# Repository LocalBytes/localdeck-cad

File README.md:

# LocalDeck CAD

## About

See exactly how the LocalDeck is put together, design your own accessories, or suggest improvements to the next revision.
These are the same mechanical and electrical design files we use to build it.

| Folder | Tool | Contents |
|---|---|---|
| [freecad](./freecad) | FreeCAD 1.1 | Enclosure, stand, key caps, moulds, and jigs. Start with [asm-localdeck](./freecad/asm-localdeck.FCStd) |
| [kicad](./kicad) | KiCad 10 | Schematic (including the face plate sheet) and PCB. The ESP32 mini footprint library is a Git submodule |

Looking to set up your LocalDeck rather than look inside it? Head to [LocalBytes Blog / KB / Refs: LocalDeck](https://blog.mylocalbytes.com/kb/2024-04-01/refs-localdeck).

## Getting started

The FreeCAD files in this repo are stored through a Git filter, so set up [Zippey](#zippey) **before** you clone.
Then clone with submodules:

```sh
git clone --recurse-submodules git@github.com:LocalBytes/localdeck-cad.git
```

Please clone the repo rather than downloading files from GitHub.
A download gives you Zippey's text format, not a file FreeCAD can open.

### Zippey

`.FCStd` files are zip archives, which Git can't diff or store efficiently.
This repo runs them through [Zippey](https://github.com/rockstorm101/zippey), which stores them unzipped and rebuilds the archive on checkout.
That way, each save only adds what actually changed.

You'll need Python on your `PATH`. Set it up once per machine:

```sh
curl -fsSL https://raw.githubusercontent.com/rockstorm101/zippey/master/zippey.py -o ~/.local/bin/zippey.py --create-dirs
git config --global filter.zippey.clean  "python ~/.local/bin/zippey.py e"
git config --global filter.zippey.smudge "python ~/.local/bin/zippey.py d"
git config --global filter.zippey.required true
```

The `required` setting makes Git stop with an error if the filter is missing, rather than quietly committing raw archives.

If you cloned before setting this up, rebuild the files with:

```sh
git ls-files -z '*.FCStd' | xargs -0 rm -f && git checkout -- '*.FCStd'
```

### Readable diffs (optional)

FreeCAD's fcinfo tool turns an `.FCStd` into a summary of each object, so `git diff` shows what changed rather than raw XML.
Install it globally, and it works in any repo:

```sh
curl -fsSL https://raw.githubusercontent.com/FreeCAD/FreeCAD/main/src/Tools/fcinfo -o ~/.local/bin/fcinfo --create-dirs
git config --global diff.fcinfo.textconv "python ~/.local/bin/fcinfo"
echo '*.FCStd diff=fcinfo' >> ~/.config/git/attributes
```

FreeCAD updates metadata such as `LastModifiedDate` on every save, so expect a few lines of that in each diff.
[GitHub / FreeCAD | src/Tools/fcinfo](https://github.com/FreeCAD/FreeCAD/blob/main/src/Tools/fcinfo)

## Contributing

Found a problem with the design, or have an idea for an improvement? [Open an issue](https://github.com/LocalBytes/localdeck-cad/issues) and tell us about it.
You'll also find plenty of LocalDeck owners on the [LocalBytes Forum](https://forum.mylocalbytes.com/), and we'd love your input there when we ask for feedback on something new.

Please talk to us in an issue before opening a pull request.
CAD files are hard to review and can't be merged like code, so we'd rather agree on a change first.
Anything you contribute becomes the property of Allport-IT LTD.

## Licence

This project is currently published with no specific licence:
- It is distributed in the hope that it will be useful, but WITHOUT ANY WARRANTY
- As an individual, you are free to learn from it and use it in your own projects
- You must not claim it as your own

Unless otherwise stated, all code is &copy; Allport-IT LTD. All rights reserved.  
"LocalBytes" and the LocalBytes Logo are &reg; of Allport-IT LTD.

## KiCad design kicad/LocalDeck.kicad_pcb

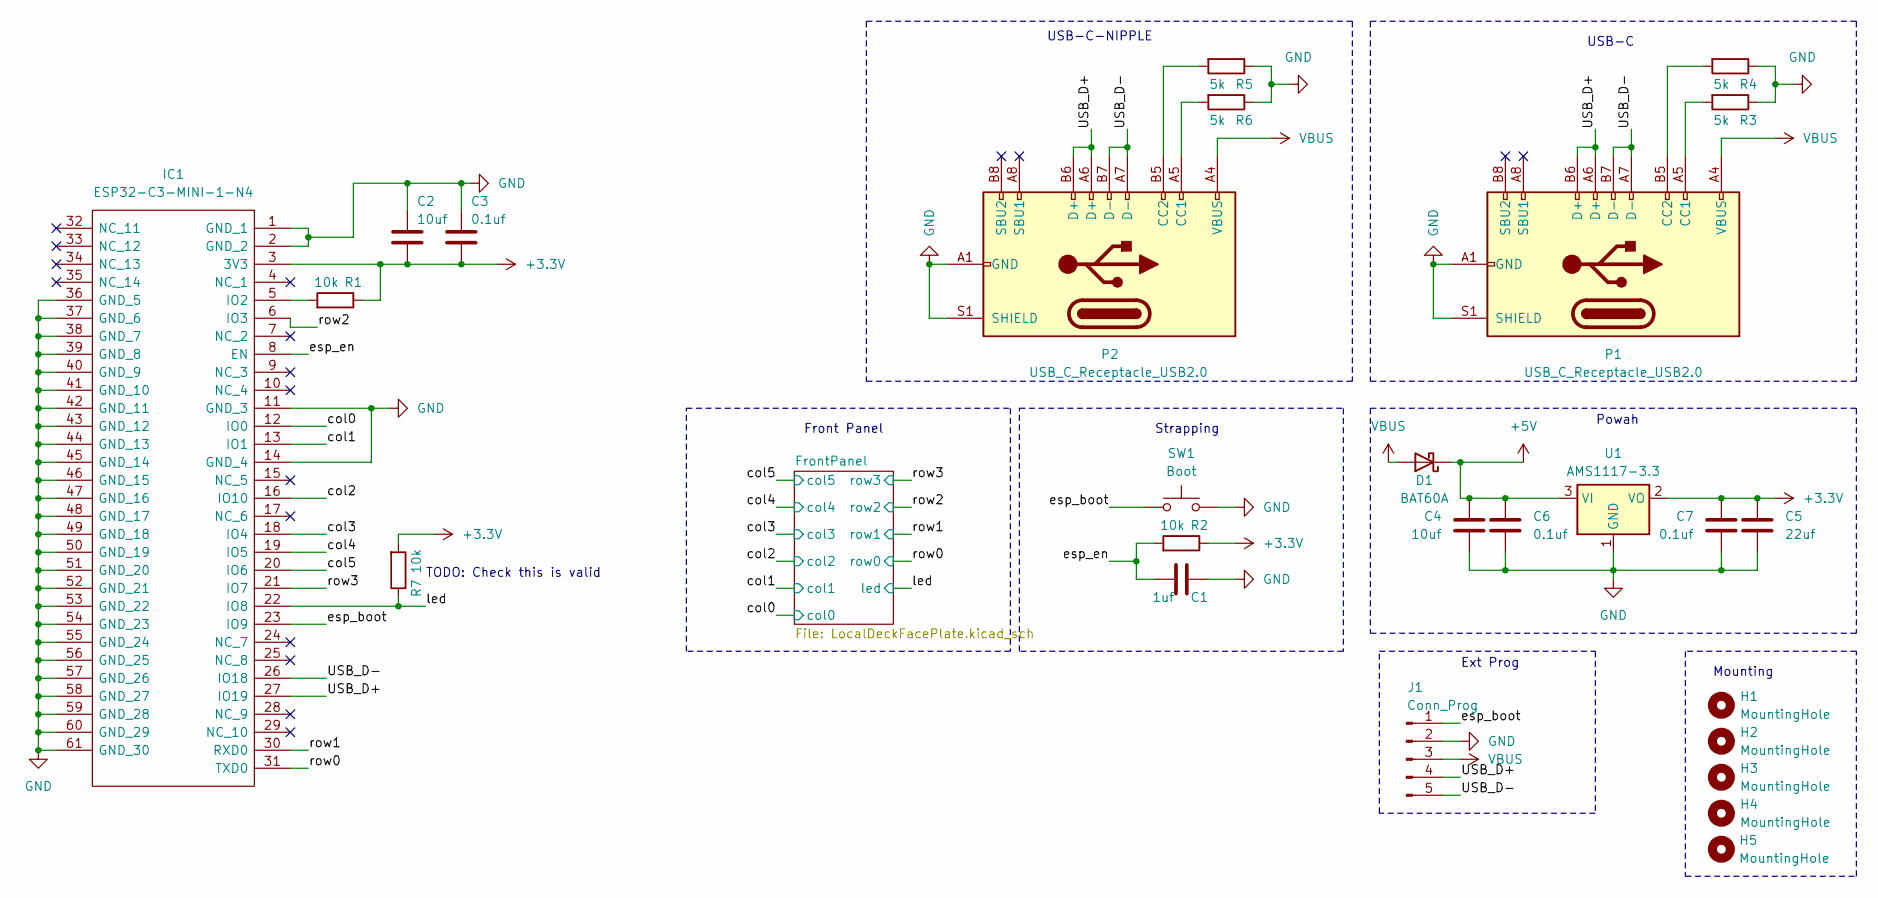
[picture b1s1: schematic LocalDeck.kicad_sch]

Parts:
C1: 1uf; C_0603_1608Metric
C2, C4: 10uf; C_0603_1608Metric
C3, C6, C7: 0.1uf; C_0603_1608Metric
C5: 22uf; C_0603_1608Metric
D1: BAT60A; D_SOD-323; JLCPCB Part C3018529
H1, H2, H3, H4, H5: MountingHole; MountingHole_3.2mm_M3
IC1: ESP32-C3-MINI-1-N4; ESP32C3MINI1N4; Manufacturer_Part_Number ESP32-C3-MINI-1-N4; Mouser Part Number 356-ESP32-C3-MINI1N4
J1: Conn_Prog; ProgrammingHeader
P1: USB_C_Receptacle_USB2.0; USB_C_Receptacle_HRO_TYPE-C-31-M-12; JLCPCB Part C165948
P2: USB_C_Receptacle_USB2.0; USB_C_Receptacle_GCT_USB4115-03-C; JLCPCB Part C2977724
R1, R2, R7: 10k; R_0603_1608Metric
R3, R4, R5, R6: 5k; R_0603_1608Metric
SW1: Boot; SW_Push_1P1T_XKB_TS-1187A; Part # TS-1187A-B-A-B; JLCPCB Part C318884
U1: AMS1117-3.3; SOT-223-3_TabPin2

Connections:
+3.3V: C2.2, C3.2, C5.1, C7.1, IC1.3 (3V3), R1.1, R2.1, R7.2, U1.2 (VO)
+5V: C4.1, C6.1, D1.1 (K), U1.3 (VI); also elsewhere on the board
/USB_D+: IC1.27 (IO19), J1.4, P1.A6 (D+), P1.B6 (D+), P2.A6 (D+), P2.B6 (D+)
/USB_D-: IC1.26 (IO18), J1.5, P1.A7 (D-), P1.B7 (D-), P2.A7 (D-), P2.B7 (D-)
/col0: IC1.12 (IO0); also elsewhere on the board
/col1: IC1.13 (IO1); also elsewhere on the board
/col2: IC1.16 (IO10); also elsewhere on the board
/col3: IC1.18 (IO4); also elsewhere on the board
/col4: IC1.19 (IO5); also elsewhere on the board
/col5: IC1.20 (IO6); also elsewhere on the board
/esp_boot: IC1.23 (IO9), J1.1, SW1.2
/esp_en: C1.1, IC1.8 (EN), R2.2
/led: IC1.22 (IO8), R7.1; also elsewhere on the board
/row0: IC1.31 (TXD0); also elsewhere on the board
/row1: IC1.30 (RXD0); also elsewhere on the board
/row2: IC1.6 (IO3); also elsewhere on the board
/row3: IC1.21 (IO7); also elsewhere on the board
GND: C1.2, C2.1, C3.1, C4.2, C5.2, C6.2, C7.2, IC1.1 (GND_1), IC1.2 (GND_2), IC1.11 (GND_3), IC1.14 (GND_4), IC1.36 (GND_5), IC1.37 (GND_6), IC1.38 (GND_7), IC1.39 (GND_8), IC1.40 (GND_9), IC1.41 (GND_10), IC1.42 (GND_11), IC1.43 (GND_12), IC1.44 (GND_13), IC1.45 (GND_14), IC1.46 (GND_15), IC1.47 (GND_16), IC1.48 (GND_17), IC1.49 (GND_18), IC1.50 (GND_19), IC1.51 (GND_20), IC1.52 (GND_21), IC1.53 (GND_22), IC1.54 (GND_23), IC1.55 (GND_24), IC1.56 (GND_25), IC1.57 (GND_26), IC1.58 (GND_27), IC1.59 (GND_28), IC1.60 (GND_29), IC1.61 (GND_30), J1.2, P1.A1 (GND), P1.A12 (GND), P1.B1 (GND), P1.B12 (GND), P1.S1 (SHIELD), P2.A1 (GND), P2.A12 (GND), P2.B1 (GND), P2.B12 (GND), P2.S1 (SHIELD), R3.1, R4.1, R5.1, R6.1, SW1.1, U1.1 (GND); also elsewhere on the board
unnamed: IC1.5 (IO2), R1.2
unnamed: P1.A5 (CC1), R3.2
unnamed: P1.B5 (CC2), R4.2
unnamed: P2.A5 (CC1), R6.2
unnamed: P2.B5 (CC2), R5.2
VBUS: D1.2 (A), J1.3, P1.A4 (VBUS), P1.A9 (VBUS), P1.B4 (VBUS), P1.B9 (VBUS), P2.A4 (VBUS), P2.A9 (VBUS), P2.B4 (VBUS), P2.B9 (VBUS)

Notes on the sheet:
Powah
Mounting
Ext Prog
USB-C
USB-C-NIPPLE
Front Panel
Strapping
TODO: Check this is valid

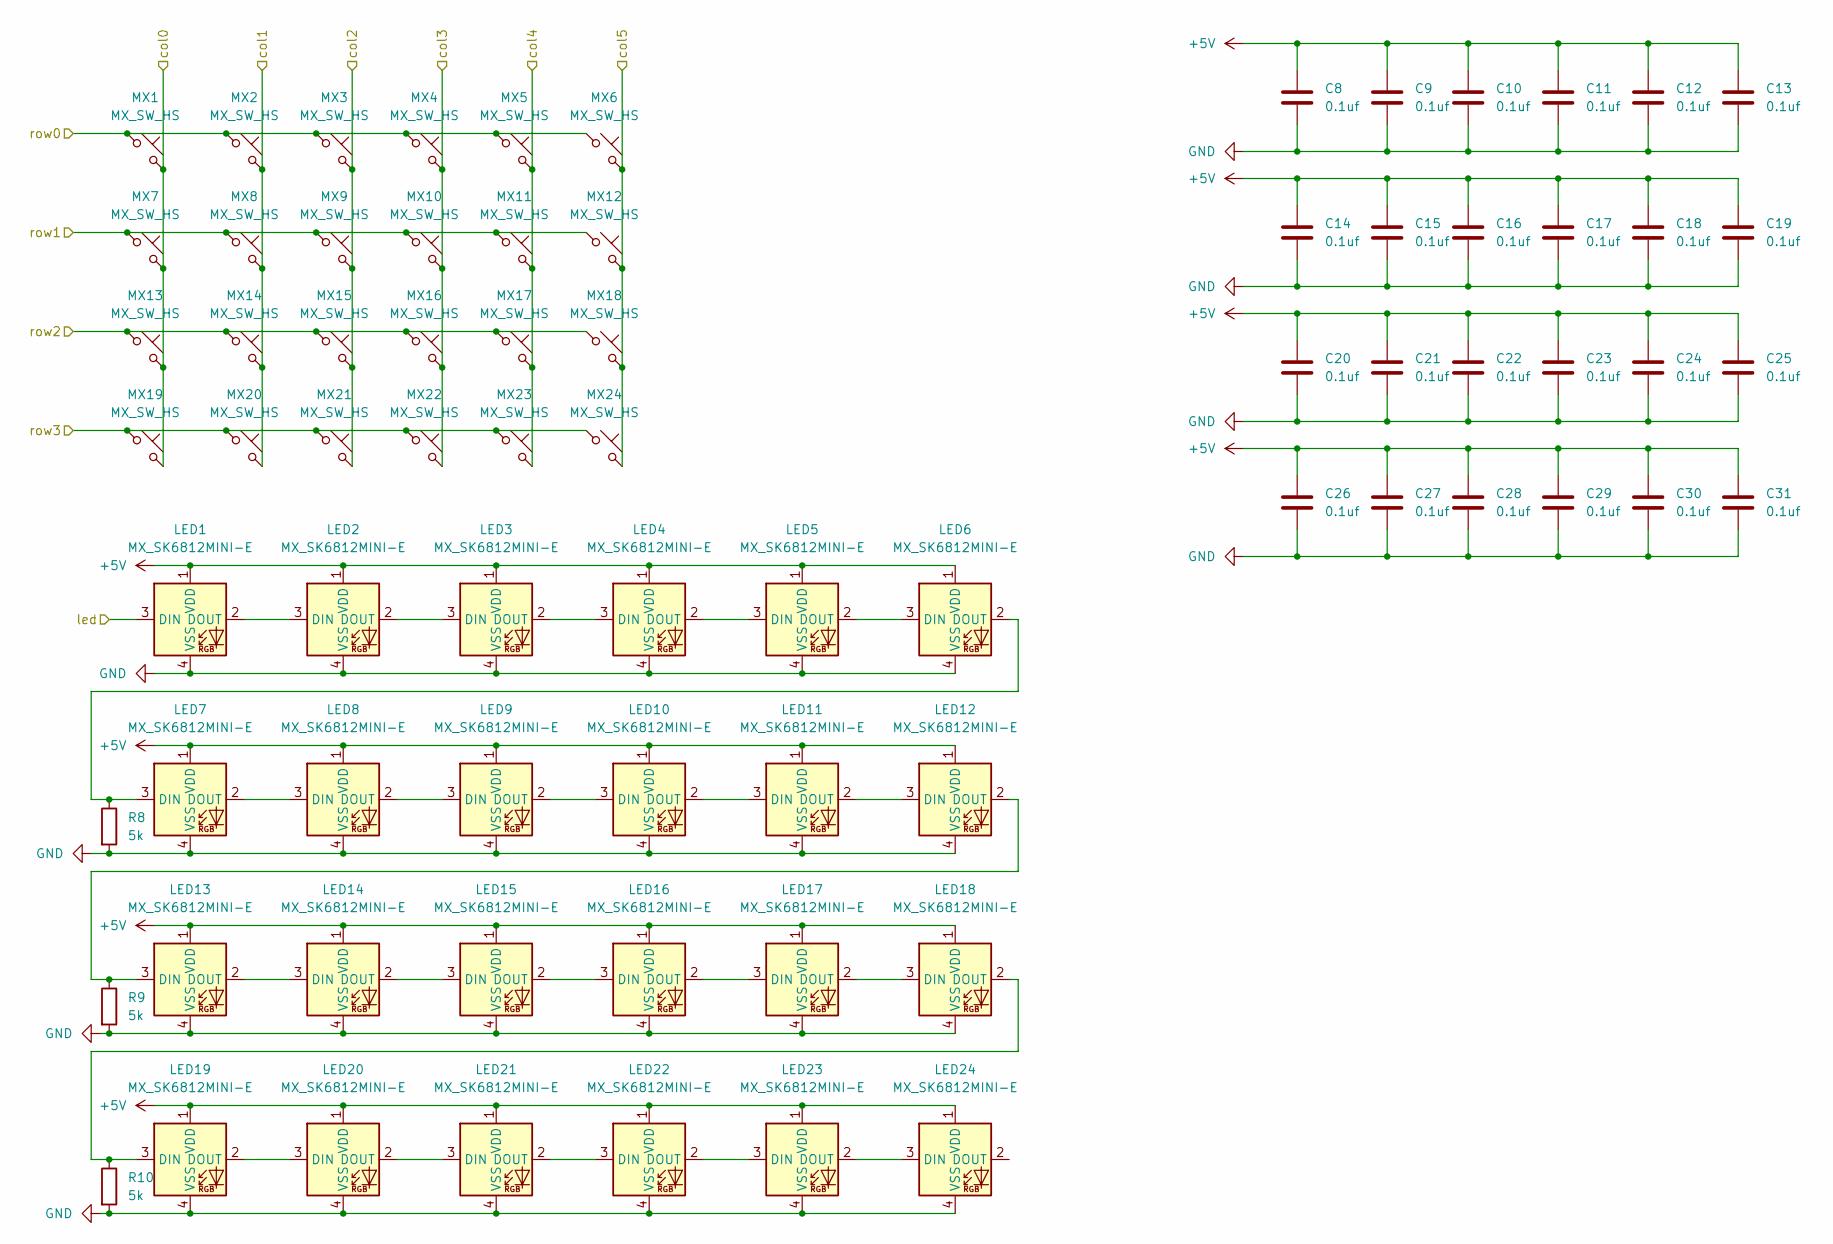
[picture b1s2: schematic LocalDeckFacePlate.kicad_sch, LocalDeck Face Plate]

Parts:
C8, C9, C10, C11, C12, C13, C14, C15, C16, C17, C18, C19, C20, C21, C22, C23, C24, C25, C26, C27, C28, C29, C30, C31: 0.1uf; C_0603_1608Metric
LED1, LED2, LED3, LED4, LED5, LED6, LED7, LED8, LED9, LED10, LED11, LED12, LED13, LED14, LED15, LED16, LED17, LED18, LED19, LED20, LED21, LED22, LED23, LED24: MX_SK6812MINI-E; LED_MX_6028R-ROT; JLCPCB Part C5149201
MX1, MX2, MX3, MX4, MX5, MX6, MX7, MX8, MX9, MX10, MX11, MX12, MX13, MX14, MX15, MX16, MX17, MX18, MX19, MX20, MX21, MX22, MX23, MX24: MX_SW_HS; SW_MX_HS_1u; JLCPCB Part C5156480
R8, R9, R10: 5k; R_0603_1608Metric

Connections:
+5V: C8.1, C9.1, C10.1, C11.1, C12.1, C13.1, C14.1, C15.1, C16.1, C17.1, C18.1, C19.1, C20.1, C21.1, C22.1, C23.1, C24.1, C25.1, C26.1, C27.1, C28.1, C29.1, C30.1, C31.1, LED1.1 (VDD), LED2.1 (VDD), LED3.1 (VDD), LED4.1 (VDD), LED5.1 (VDD), LED6.1 (VDD), LED7.1 (VDD), LED8.1 (VDD), LED9.1 (VDD), LED10.1 (VDD), LED11.1 (VDD), LED12.1 (VDD), LED13.1 (VDD), LED14.1 (VDD), LED15.1 (VDD), LED16.1 (VDD), LED17.1 (VDD), LED18.1 (VDD), LED19.1 (VDD), LED20.1 (VDD), LED21.1 (VDD), LED22.1 (VDD), LED23.1 (VDD), LED24.1 (VDD); also elsewhere on the board
/col0: MX1.2, MX7.2, MX13.2, MX19.2; also elsewhere on the board
/col1: MX2.2, MX8.2, MX14.2, MX20.2; also elsewhere on the board
/col2: MX3.2, MX9.2, MX15.2, MX21.2; also elsewhere on the board
/col3: MX4.2, MX10.2, MX16.2, MX22.2; also elsewhere on the board
/col4: MX5.2, MX11.2, MX17.2, MX23.2; also elsewhere on the board
/col5: MX6.2, MX12.2, MX18.2, MX24.2; also elsewhere on the board
/led: LED1.3 (DIN); also elsewhere on the board
/row0: MX1.1, MX2.1, MX3.1, MX4.1, MX5.1, MX6.1; also elsewhere on the board
/row1: MX7.1, MX8.1, MX9.1, MX10.1, MX11.1, MX12.1; also elsewhere on the board
/row2: MX13.1, MX14.1, MX15.1, MX16.1, MX17.1, MX18.1; also elsewhere on the board
/row3: MX19.1, MX20.1, MX21.1, MX22.1, MX23.1, MX24.1; also elsewhere on the board
GND: C8.2, C9.2, C10.2, C11.2, C12.2, C13.2, C14.2, C15.2, C16.2, C17.2, C18.2, C19.2, C20.2, C21.2, C22.2, C23.2, C24.2, C25.2, C26.2, C27.2, C28.2, C29.2, C30.2, C31.2, LED1.4 (VSS), LED2.4 (VSS), LED3.4 (VSS), LED4.4 (VSS), LED5.4 (VSS), LED6.4 (VSS), LED7.4 (VSS), LED8.4 (VSS), LED9.4 (VSS), LED10.4 (VSS), LED11.4 (VSS), LED12.4 (VSS), LED13.4 (VSS), LED14.4 (VSS), LED15.4 (VSS), LED16.4 (VSS), LED17.4 (VSS), LED18.4 (VSS), LED19.4 (VSS), LED20.4 (VSS), LED21.4 (VSS), LED22.4 (VSS), LED23.4 (VSS), LED24.4 (VSS), R8.2, R9.2, R10.2; also elsewhere on the board
unnamed: LED1.2 (DOUT), LED2.3 (DIN)
unnamed: LED2.2 (DOUT), LED3.3 (DIN)
unnamed: LED3.2 (DOUT), LED4.3 (DIN)
unnamed: LED4.2 (DOUT), LED5.3 (DIN)
unnamed: LED5.2 (DOUT), LED6.3 (DIN)
unnamed: LED6.2 (DOUT), LED7.3 (DIN), R8.1
unnamed: LED7.2 (DOUT), LED8.3 (DIN)
unnamed: LED8.2 (DOUT), LED9.3 (DIN)
unnamed: LED9.2 (DOUT), LED10.3 (DIN)
unnamed: LED10.2 (DOUT), LED11.3 (DIN)
unnamed: LED11.2 (DOUT), LED12.3 (DIN)
unnamed: LED12.2 (DOUT), LED13.3 (DIN), R9.1
unnamed: LED13.2 (DOUT), LED14.3 (DIN)
unnamed: LED14.2 (DOUT), LED15.3 (DIN)
unnamed: LED15.2 (DOUT), LED16.3 (DIN)
unnamed: LED16.2 (DOUT), LED17.3 (DIN)
unnamed: LED17.2 (DOUT), LED18.3 (DIN)
unnamed: LED18.2 (DOUT), LED19.3 (DIN), R10.1
unnamed: LED19.2 (DOUT), LED20.3 (DIN)
unnamed: LED20.2 (DOUT), LED21.3 (DIN)
unnamed: LED21.2 (DOUT), LED22.3 (DIN)
unnamed: LED22.2 (DOUT), LED23.3 (DIN)
unnamed: LED23.2 (DOUT), LED24.3 (DIN)

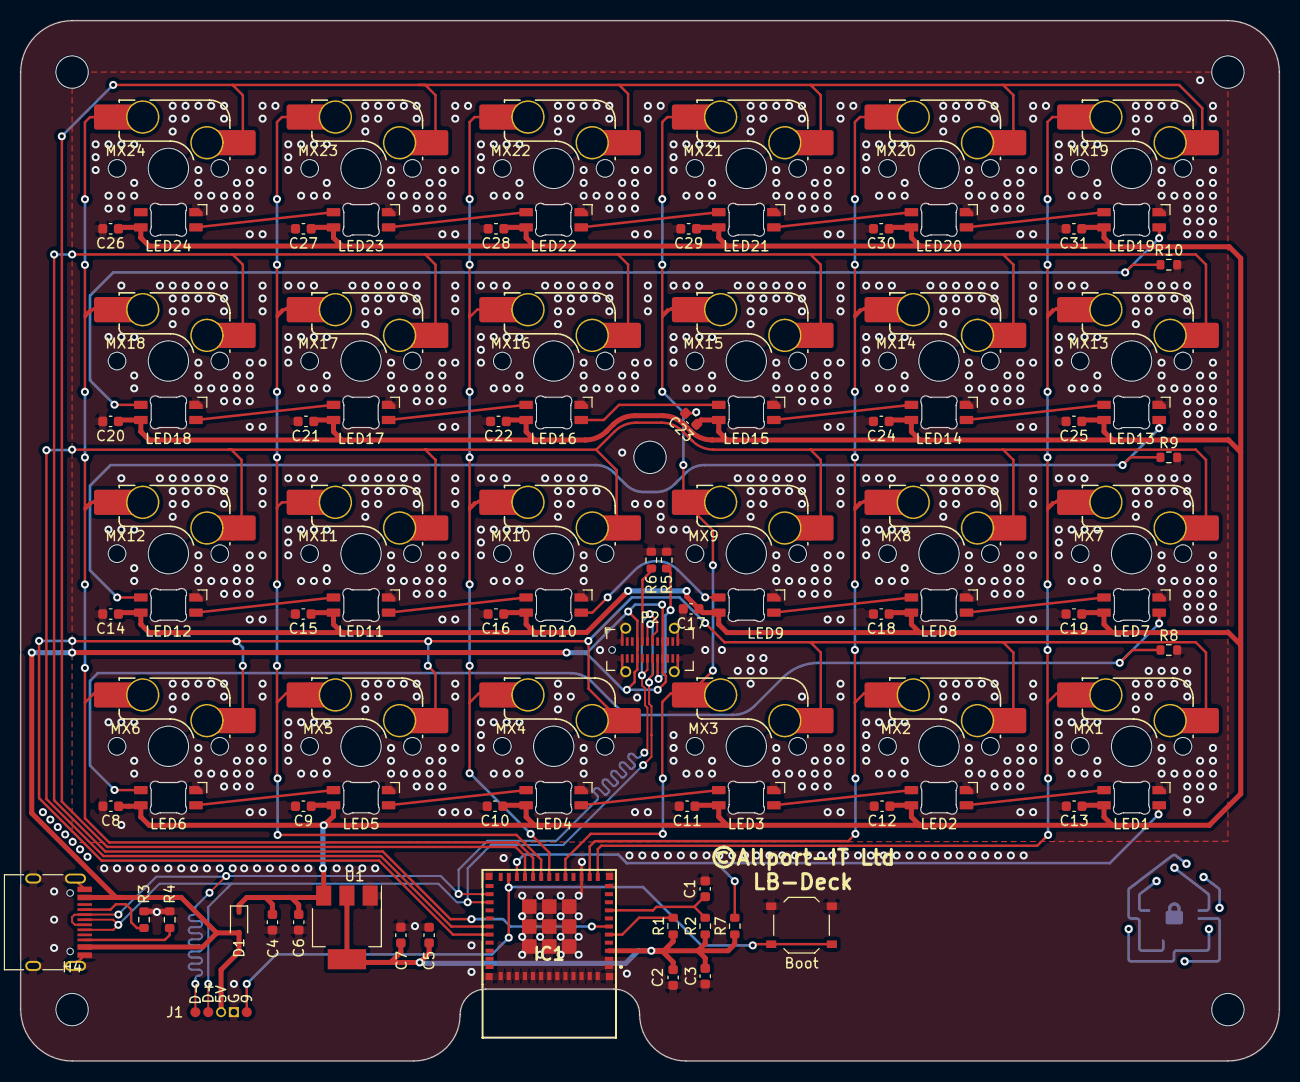
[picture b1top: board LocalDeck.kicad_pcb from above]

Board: 2 copper layers, 124.5 x 102.9 mm, 101 parts (0 on the bottom side), 47 nets.

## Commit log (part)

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2024-07-26 Inital Commit
2024-07-26 Inital Commit - Adding everything
2024-07-26 fix: :shushing_face:
2024-07-30 feat: Added programming Header
2024-07-31 chore: Removed unused part
2024-07-31 feat: Made enclosure compatable with new feet
2024-07-31 feat: Updated asm-enclosure to show new feet
2024-08-02 chore: Added exports to ignore
2024-08-02 feat(freecad): Increased snap-fit thickness
2024-08-07 feat(freecad): Added usb-c part for clearance
2024-08-07 refactor(freecad): Moved `part-cap` to `part-key-cap`
2024-08-07 feat(freecad): Moved asm-key to Ondsel Assembly
2024-08-07 feat(freecad): Rebuilt main assembly
2024-08-07 fix: Unlocks all
2024-08-07 fix: Added more USB Clearance
2024-08-14 feat(freecad): Added boot hole & stats window
2024-08-14 chore(kicad): Added measurements & part numbers
2024-08-14 chore: Removed text mode from FCStd
2024-08-18 chore: Latest FCad version, previous didn't calculate suptractive patterns properly!
2024-12-22 chore: FreeCAD 1.0.0
2025-02-03 feat(kicad): Added LED decoupling capacitors
    Adds a 0.1uF decoupling capacitor for each of the 24 SK6812 LEDs (C8 to C31) and three 5k resistors (R8 to R10), and reroutes the board to fit them.
    Recovered from KiCad's project backups.
2025-04-03 chore(kicad): KiCad 9 and routing fixes for production
    Upgrades the project to KiCad 9 and tidies the routing ahead of the April 2025 PCBA order.
    Recovered from KiCad's project backups.
2026-01-08 chore(kicad): Silkscreen clean-up
    Removes hidden footprint text from the silkscreen.
    Recovered from KiCad's project backups.

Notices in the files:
kicad/LocalDeck.kicad_pcb:
Licence: https://github.com/LocalBytes/localdeck-cad#licence
